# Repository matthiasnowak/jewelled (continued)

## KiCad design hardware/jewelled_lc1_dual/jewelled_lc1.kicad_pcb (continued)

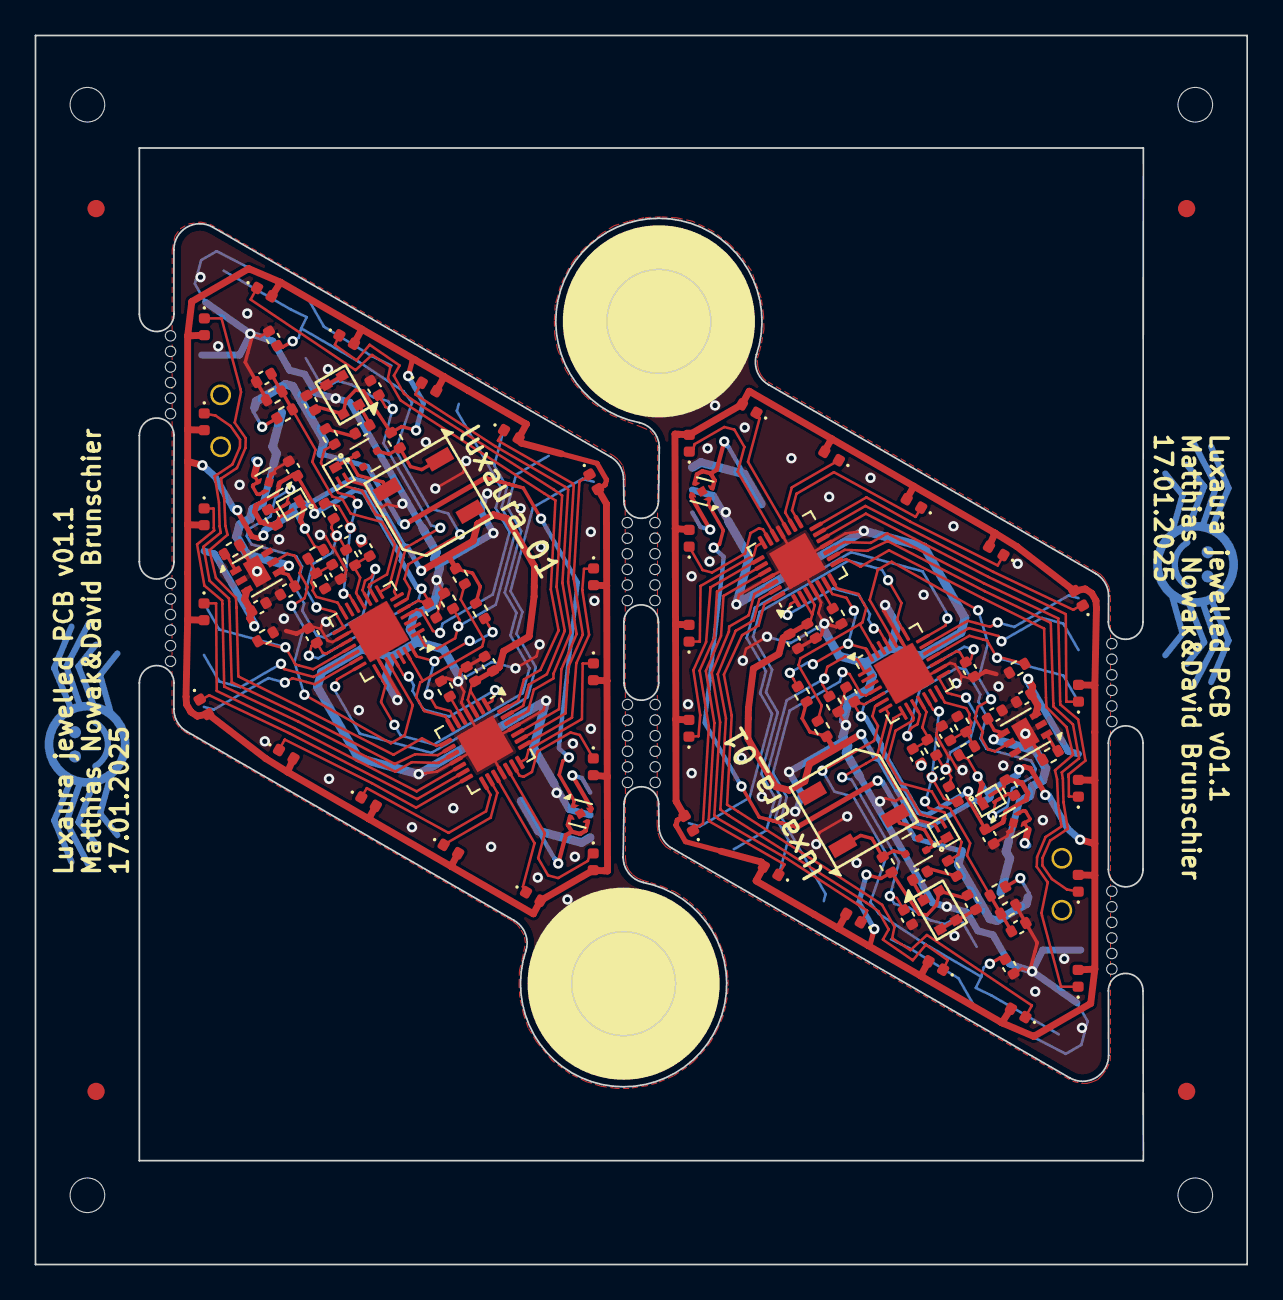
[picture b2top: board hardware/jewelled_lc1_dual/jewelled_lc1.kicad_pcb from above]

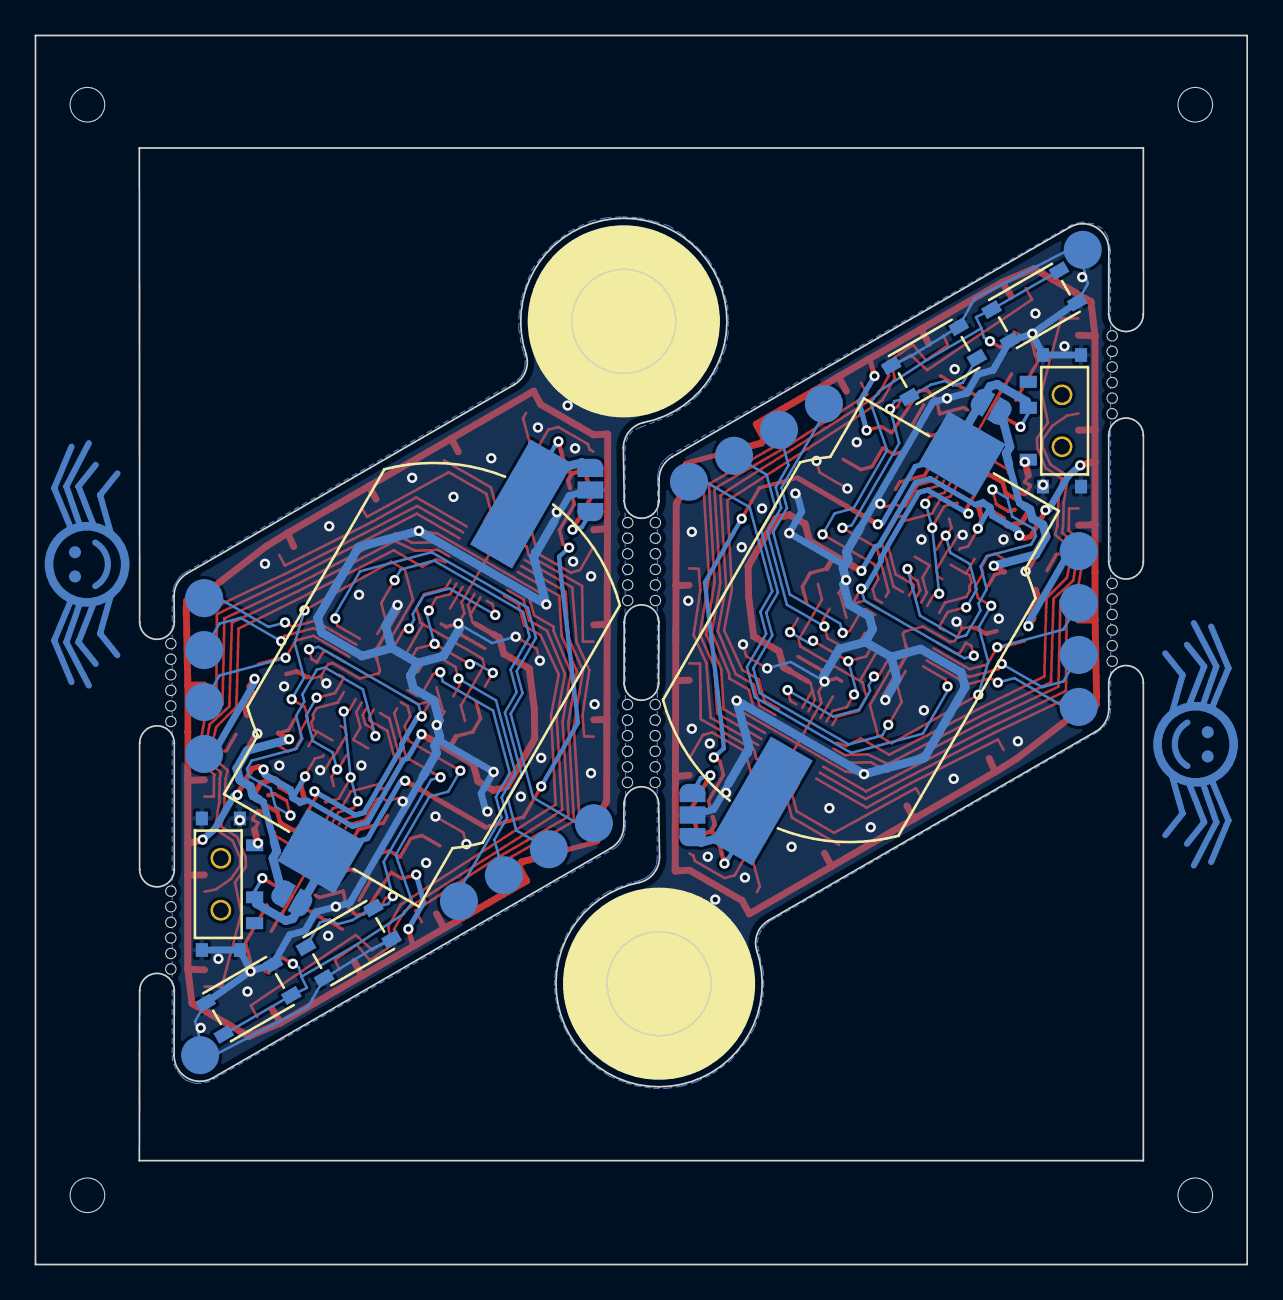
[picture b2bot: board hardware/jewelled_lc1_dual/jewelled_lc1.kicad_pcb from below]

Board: 2 copper layers, 70.0 x 71.0 mm, 148 parts (18 on the bottom side), 106 nets.

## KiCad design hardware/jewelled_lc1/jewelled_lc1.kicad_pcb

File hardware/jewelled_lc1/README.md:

# LuxAura 01 Earring Hardware

## Hardware Overview

- WIP

## Notes

- WIP
- Please note the correct jumper settings to allow either CR2032 or LIR2032 use (bridging the charging circuit)

## Images

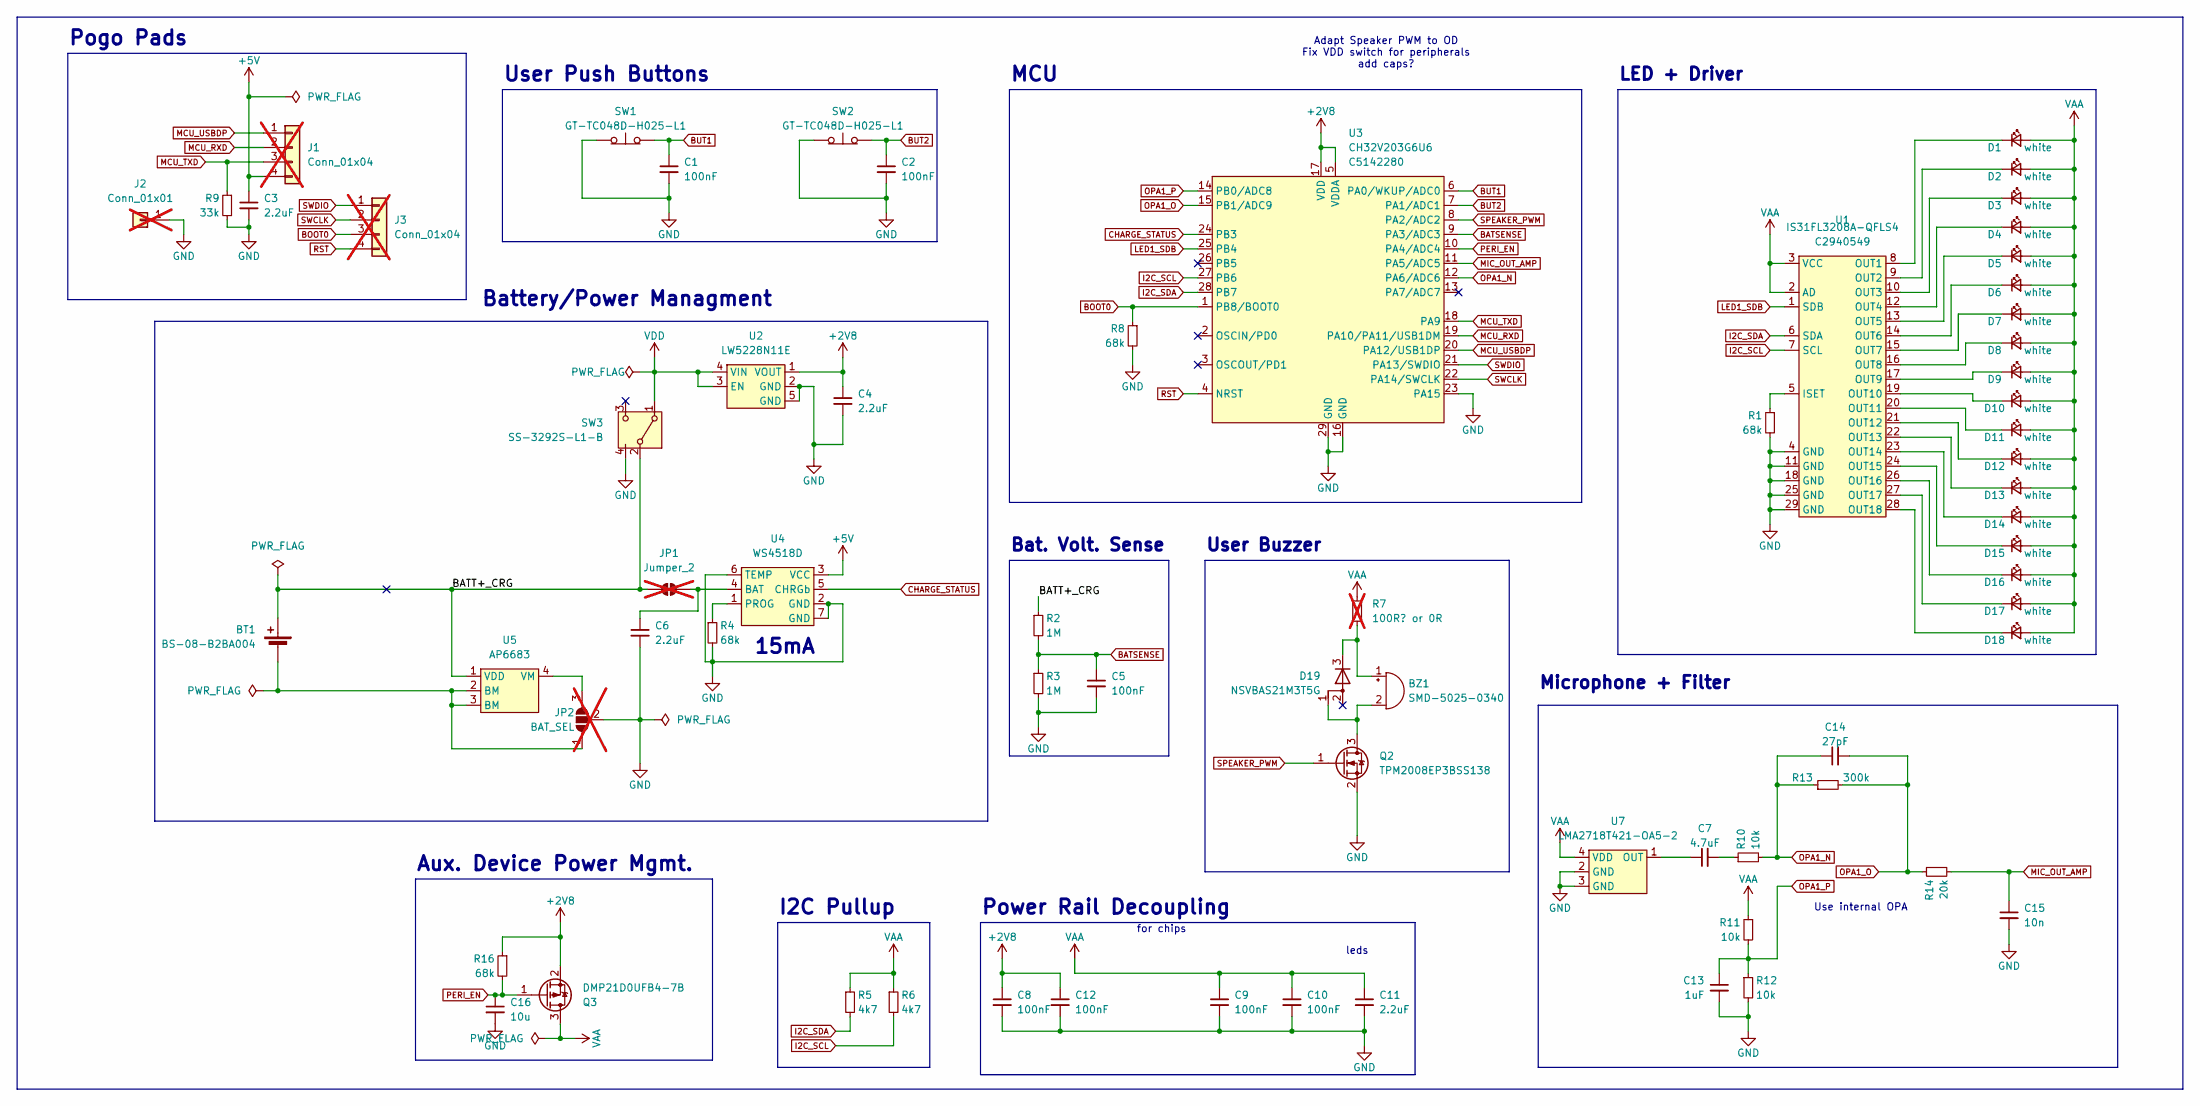
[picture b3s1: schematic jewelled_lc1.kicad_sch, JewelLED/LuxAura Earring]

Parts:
BT1: BS-08-B2BA004; LCSC C964780
BZ1: SMD-5025-0340
C1, C2, C5, C8, C9, C10, C12: 100nF; C_0402_1005Metric; LCSC C100072
C3, C4, C6, C11: 2.2uF; C_0402_1005Metric; LCSC C14445
C7: 4.7uF; C_0402_1005Metric
C13: 1uF; C_0402_1005Metric
C14: 27pF; C_0402_1005Metric
C15: 10n; C_0402_1005Metric
C16: 10u; C_0402_1005Metric; LCSC C14445
D1, D2, D3, D4, D5, D6, D7, D8, D9, D10, D11, D12, D13, D14, D15, D16, D17, D18: white; LED_0402_1005Metric; LCSC C20613596
D19: NSVBAS21M3T5G; SOT-723; LCSC C896450
J1, J3: Conn_01x04; pogo_conn_01x03_P2.0mm_angled; not fitted
J2: Conn_01x01; pogo_conn_01x01_P2.0mm; not fitted
JP1: Jumper_2; SolderJumper-2_P1.3mm_Open_RoundedPad1.0x1.5mm_NoSilk; not fitted
JP2: BAT_SEL; SolderJumper-3_P1.3mm_Open_RoundedPad1.0x1.5mm_NoSilk; not fitted
Q2: TPM2008EP3BSS138; DFN-3_1.0x0.6mm_P0.35mm; MPN C2682293
Q3: DMP21D0UFB4-7B; DFN-3_1.0x0.6mm_P0.35mm; LCSC C155329
R1, R4, R8, R16: 68k; R_0402_1005Metric
R2, R3: 1M; R_0402_1005Metric; LCSC C26083
R5, R6: 4k7; R_0402_1005Metric; LCSC C25940
R7: 100R? or 0R; R_0402_1005Metric; not fitted
R9: 33k; R_0402_1005Metric; MPN C25779; LCSC C25779
R10, R11, R12: 10k; R_0402_1005Metric
R13: 300k; R_0402_1005Metric
R14: 20k; R_0402_1005Metric
SW1, SW2: GT-TC048D-H025-L1; LCSC C843674
SW3: SS-3292S-L1-B; LCSC C2681570
U1: IS31FL3208A-QFLS4; QFN-28-1EP_4x4mm_P0.4mm_EP2.4x2.4mm; MPN C2940549; LCSC C2940551
U2: LW5228N11E; UDFN-4-1EP_1x1mm_P0.65mm_EP0.48x0.48mm; LCSC C20630428
U3: CH32V203G6U6; QFN-28-1EP_4x4mm_P0.4mm_EP2.6x2.6mm; MPN C5142280; LCSC C5142280
U4: WS4518D; DFN-6-1EP_2x2mm_P0.65mm_EP1x1.6mm; LCSC C910991
U5: AP6683; UDFN-4-1EP_1x1mm_P0.65mm_EP0.48x0.48mm; LCSC C2849565
U7: LMA2718T421-OA5-2; ZTS6117H; LCSC C2999748

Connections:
+2V8: C4.1, C8.1, C12.1, Q3.2 (S), R16.1, U2.1 (VOUT), U3.5 (VDDA), U3.17 (VDD)
+5V: C3.1, J1.4, U4.3 (VCC)
/BATT+_CRG: BT1.1 (+), JP1.1 (A), R2.1, SW3.2 (B), U5.1 (VDD)
BATSENSE: C5.1, R2.2, R3.1, U3.9 (PA3/ADC3)
BOOT0: J3.3, R8.1, U3.1 (PB8/BOOT0)
BUT1: C1.1, SW1.2 (B), U3.6 (PA0/WKUP/ADC0)
BUT2: C2.1, SW2.2 (B), U3.7 (PA1/ADC1)
CHARGE_STATUS: U3.24 (PB3), U4.5 (CHRGb)
GND: C1.2, C2.2, C3.2, C4.2, C5.2, C6.2, C8.2, C9.2, C10.2, C11.2, C12.2, C13.2, C15.2, C16.2, J2.1, JP2.2 (C), Q2.2 (S), R1.2, R3.2, R4.2, R8.2, R9.2, R12.2, SW1.1 (A), SW2.1 (A), SW3.4 (B), U1.4 (GND), U1.11 (GND), U1.18 (GND), U1.25 (GND), U1.29 (GND), U2.2 (GND), U2.5 (GND), U3.16 (GND), U3.23 (PA15), U3.29 (GND), U4.2 (GND), U4.6 (TEMP), U4.7 (GND), U7.2 (GND), U7.3 (GND)
I2C_SCL: R6.2, U1.7 (SCL), U3.27 (PB6)
I2C_SDA: R5.2, U1.6 (SDA), U3.28 (PB7)
LED1_SDB: U1.1 (SDB), U3.25 (PB4)
MCU_RXD: J1.2, U3.19 (PA10/PA11/USB1DM)
MCU_TXD: J1.3, R9.1, U3.18 (PA9)
MCU_USBDP: J1.1, U3.20 (PA12/USB1DP)
MIC_OUT_AMP: C15.1, R14.2, U3.11 (PA5/ADC5)
unnamed: BT1.2 (-), JP2.1 (A), U5.2 (BM), U5.3 (BM)
unnamed: BZ1.1 (+), D19.3 (K), R7.2
unnamed: BZ1.2 (-), D19.1 (A), Q2.3 (D)
unnamed: C7.2, R10.1
unnamed: D1.1 (K), U1.8 (OUT1)
unnamed: D2.1 (K), U1.9 (OUT2)
unnamed: D3.1 (K), U1.10 (OUT3)
unnamed: D4.1 (K), U1.12 (OUT4)
unnamed: D5.1 (K), U1.13 (OUT5)
unnamed: D6.1 (K), U1.14 (OUT6)
unnamed: D7.1 (K), U1.15 (OUT7)
unnamed: D8.1 (K), U1.16 (OUT8)
unnamed: D9.1 (K), U1.17 (OUT9)
unnamed: D10.1 (K), U1.19 (OUT10)
unnamed: D11.1 (K), U1.20 (OUT11)
unnamed: D12.1 (K), U1.21 (OUT12)
unnamed: D13.1 (K), U1.22 (OUT13)
unnamed: D14.1 (K), U1.23 (OUT14)
unnamed: D15.1 (K), U1.24 (OUT15)
unnamed: D16.1 (K), U1.26 (OUT16)
unnamed: D17.1 (K), U1.27 (OUT17)
unnamed: D18.1 (K), U1.28 (OUT18)
unnamed: C6.1, JP1.2 (B), U4.4 (BAT)
unnamed: JP2.3 (B), U5.4 (VM)
unnamed: R1.1, U1.5 (ISET)
unnamed: R4.1, U4.1 (PROG)
unnamed: C7.1, U7.1 (OUT)
OPA1_N: C14.1, R10.2, R13.1, U3.12 (PA6/ADC6)
OPA1_O: C14.2, R13.2, R14.1, U3.15 (PB1/ADC9)
OPA1_P: C13.1, R11.2, R12.1, U3.14 (PB0/ADC8)
PERI_EN: C16.1, Q3.1 (G), R16.2, U3.10 (PA4/ADC4)
RST: J3.4, U3.4 (NRST)
SPEAKER_PWM: Q2.1 (G), U3.8 (PA2/ADC2)
SWCLK: J3.2, U3.22 (PA14/SWCLK)
SWDIO: J3.1, U3.21 (PA13/SWDIO)
VAA: C9.1, C10.1, C11.1, D1.2 (A), D2.2 (A), D3.2 (A), D4.2 (A), D5.2 (A), D6.2 (A), D7.2 (A), D8.2 (A), D9.2 (A), D10.2 (A), D11.2 (A), D12.2 (A), D13.2 (A), D14.2 (A), D15.2 (A), D16.2 (A), D17.2 (A), D18.2 (A), Q3.3 (D), R5.1, R6.1, R7.1, R11.1, U1.2 (AD), U1.3 (VCC), U7.4 (VDD)
VDD: SW3.1 (A), U2.3 (EN), U2.4 (VIN)

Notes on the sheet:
leds
User Push Buttons
Use internal OPA
Microphone + Filter
MCU
User Buzzer
Pogo Pads
Battery/Power Managment
15mA
Adapt Speaker PWM to OD Fix VDD switch for peripherals add caps?
LED + Driver
Power Rail Decoupling
Aux. Device Power Mgmt.
I2C Pullup
for chips
Bat. Volt. Sense

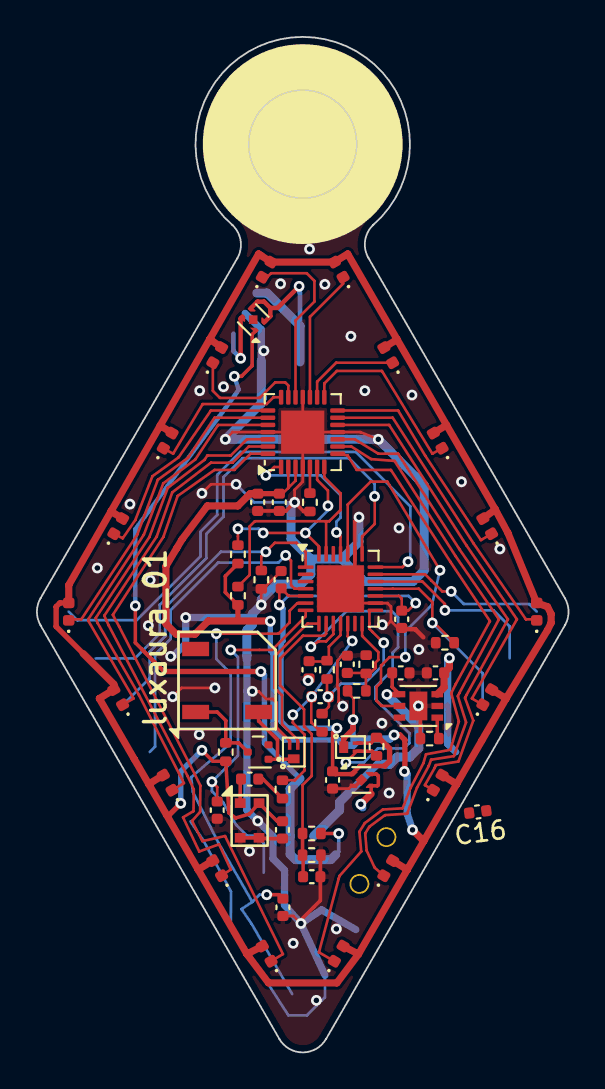
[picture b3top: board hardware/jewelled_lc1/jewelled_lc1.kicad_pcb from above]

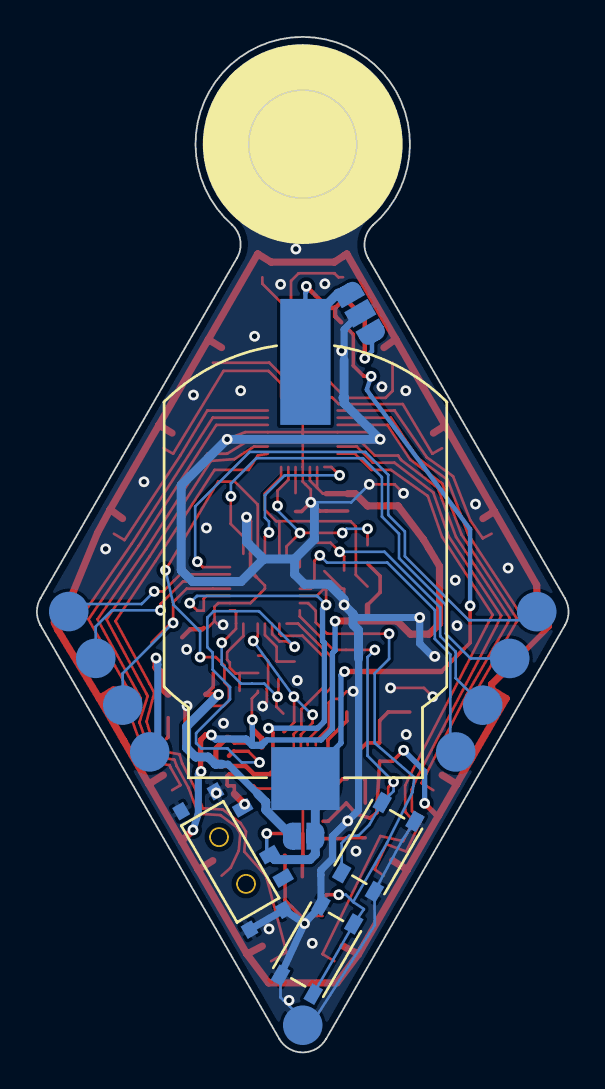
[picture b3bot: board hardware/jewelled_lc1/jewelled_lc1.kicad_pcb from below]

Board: 2 copper layers, 29.5 x 56.4 mm, 68 parts (9 on the bottom side), 53 nets.

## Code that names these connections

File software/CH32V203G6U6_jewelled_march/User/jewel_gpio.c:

/*
 * jewel_gpio.c
 *
 *  Created on: 3 Mar 2025
 *      Author: matth
 */

#include "jewel_gpio.h"

void GPIO_Init_Config(void) {
    RCC_APB2PeriphClockCmd(RCC_APB2Periph_GPIOA, ENABLE);
    RCC_APB2PeriphClockCmd(RCC_APB2Periph_GPIOB, ENABLE);
    GPIO_InitTypeDef GPIO_InitStructure = {0};

    // GPIOB_0:     OPA1_P
    GPIO_InitStructure.GPIO_Pin = IO_OPA_P_PIN;
    GPIO_InitStructure.GPIO_Mode = GPIO_Mode_IN_FLOATING;
    GPIO_InitStructure.GPIO_Speed = GPIO_Speed_10MHz;
    GPIO_Init(IO_OPA_P_PORT, &GPIO_InitStructure);

    // GPIOA_6:     OPA1_N
    GPIO_InitStructure.GPIO_Pin = IO_OPA_N_PIN;
    GPIO_InitStructure.GPIO_Mode = GPIO_Mode_IN_FLOATING;
    GPIO_InitStructure.GPIO_Speed = GPIO_Speed_10MHz;
    GPIO_Init(IO_OPA_N_PORT, &GPIO_InitStructure);

    // GPIOB_1:     Dont init OPA1_OUT1 as GPIO
//    GPIO_InitStructure.GPIO_Pin = IO_OPA_O_PIN;
//    GPIO_InitStructure.GPIO_Mode = GPIO_Mode_AIN;
//    GPIO_InitStructure.GPIO_Speed = GPIO_Speed_10MHz;
//    GPIO_Init(IO_OPA_O_PORT, &GPIO_InitStructure);

    // GPIOA_5:     MICOUT
    GPIO_InitStructure.GPIO_Pin = IO_MICOUT_PIN;
    GPIO_InitStructure.GPIO_Mode = GPIO_Mode_AIN;
    GPIO_InitStructure.GPIO_Speed = GPIO_Speed_10MHz;
    GPIO_Init(IO_MICOUT_PORT, &GPIO_InitStructure);

    // GPIOA_0:     BUT1
    GPIO_InitStructure.GPIO_Pin = GPIO_Pin_0;
    GPIO_InitStructure.GPIO_Mode = GPIO_Mode_IPU;
    GPIO_InitStructure.GPIO_Speed = GPIO_Speed_50MHz;
    GPIO_Init(GPIOA, &GPIO_InitStructure);

    // GPIOA_1:     BUT2
    GPIO_InitStructure.GPIO_Pin = GPIO_Pin_1;
    GPIO_InitStructure.GPIO_Mode = GPIO_Mode_IPU;
    GPIO_InitStructure.GPIO_Speed = GPIO_Speed_50MHz;
    GPIO_Init(IO_BUT2_PORT, &GPIO_InitStructure);

    // GPIOA_2:     BUZZER
    GPIO_StructInit(&GPIO_InitStructure);
    GPIO_InitStructure.GPIO_Pin = IO_BUZZ_PIN;
    GPIO_InitStructure.GPIO_Mode = GPIO_Mode_Out_PP;
    GPIO_InitStructure.GPIO_Speed = GPIO_Speed_10MHz;
    GPIO_Init(IO_BUZZ_PORT, &GPIO_InitStructure);

    //    // GPIOA_4:     PERI_EN
    GPIO_WriteBit(IO_PERI_PORT, IO_PERI_PIN, Bit_SET); // Peripheral off
    GPIO_InitStructure.GPIO_Pin = IO_PERI_PIN;
    GPIO_InitStructure.GPIO_Mode = GPIO_Mode_Out_OD;
    GPIO_InitStructure.GPIO_Speed = GPIO_Speed_10MHz;
    GPIO_Init(IO_PERI_PORT, &GPIO_InitStructure);

    // GPIOA_3:     BATSENSE
    GPIO_StructInit(&GPIO_InitStructure);
    GPIO_InitStructure.GPIO_Pin = IO_BAT_PIN;
    GPIO_InitStructure.GPIO_Mode = GPIO_Mode_AIN;
    GPIO_InitStructure.GPIO_Speed = GPIO_Speed_10MHz;
    GPIO_Init(IO_BAT_PORT, &GPIO_InitStructure);

    // GPIOB_3:     CHARGESTATE
    GPIO_StructInit(&GPIO_InitStructure);
    GPIO_InitStructure.GPIO_Pin = IO_CHARGE_PIN;
    GPIO_InitStructure.GPIO_Mode = GPIO_Mode_IPU;
    GPIO_InitStructure.GPIO_Speed = GPIO_Speed_10MHz;
    GPIO_Init(IO_CHARGE_PORT, &GPIO_InitStructure);

    // GPIOB_8:     BOOT0
    GPIO_StructInit(&GPIO_InitStructure);
    GPIO_InitStructure.GPIO_Pin = IO_BOOT0_PIN;
    GPIO_InitStructure.GPIO_Mode = GPIO_Mode_IN_FLOATING;
    GPIO_InitStructure.GPIO_Speed = GPIO_Speed_10MHz;
    GPIO_Init(IO_BOOT0_PORT, &GPIO_InitStructure);

    // GPIOB_6:     SCL
    GPIO_StructInit(&GPIO_InitStructure);
    GPIO_InitStructure.GPIO_Pin = IO_SCL_PIN;
    GPIO_InitStructure.GPIO_Mode = GPIO_Mode_AF_OD;
    GPIO_InitStructure.GPIO_Speed = GPIO_Speed_50MHz;
    GPIO_Init(IO_SCL_PORT, &GPIO_InitStructure);

    // GPIOB_7:     SDA
    GPIO_StructInit(&GPIO_InitStructure);
    GPIO_InitStructure.GPIO_Pin = IO_SDA_PIN;
    GPIO_InitStructure.GPIO_Mode = GPIO_Mode_AF_OD;
    GPIO_InitStructure.GPIO_Speed = GPIO_Speed_50MHz;
    GPIO_Init(IO_SDA_PORT, &GPIO_InitStructure);

    // GPIOB_7:     SDB
    GPIO_StructInit(&GPIO_InitStructure);
    GPIO_InitStructure.GPIO_Pin = IO_LED_SDB_PIN;
    GPIO_InitStructure.GPIO_Mode = GPIO_Mode_Out_PP;
    GPIO_InitStructure.GPIO_Speed = GPIO_Speed_10MHz;
    GPIO_Init(IO_LED_SDB_PORT, &GPIO_InitStructure);

    // GPIOA_9:     TX
    GPIO_StructInit(&GPIO_InitStructure);
    GPIO_InitStructure.GPIO_Pin = GPIO_Pin_9;
    GPIO_InitStructure.GPIO_Mode = GPIO_Mode_AF_PP;
    //GPIO_InitStructure.GPIO_Mode = GPIO_Mode_IN_FLOATING;
    GPIO_InitStructure.GPIO_Speed = GPIO_Speed_50MHz;
    GPIO_Init(GPIOA, &GPIO_InitStructure);

    // GPIOA_10:     RX
    GPIO_StructInit(&GPIO_InitStructure);
    GPIO_InitStructure.GPIO_Pin = GPIO_Pin_10;
    GPIO_InitStructure.GPIO_Mode = GPIO_Mode_IN_FLOATING;
    GPIO_InitStructure.GPIO_Speed = GPIO_Speed_50MHz;
    GPIO_Init(GPIOA, &GPIO_InitStructure);

    GPIO_StructInit(&GPIO_InitStructure);
    GPIO_InitStructure.GPIO_Pin = GPIO_Pin_13;
    GPIO_InitStructure.GPIO_Mode = GPIO_Mode_IN_FLOATING;
    GPIO_InitStructure.GPIO_Speed = GPIO_Speed_50MHz;
    GPIO_Init(GPIOA, &GPIO_InitStructure);

    GPIO_StructInit(&GPIO_InitStructure);
    GPIO_InitStructure.GPIO_Pin = GPIO_Pin_12;
    GPIO_InitStructure.GPIO_Mode = GPIO_Mode_IN_FLOATING;
    GPIO_InitStructure.GPIO_Speed = GPIO_Speed_50MHz;
    GPIO_Init(GPIOA, &GPIO_InitStructure);

    GPIO_StructInit(&GPIO_InitStructure);
    GPIO_InitStructure.GPIO_Pin = GPIO_Pin_11;
    GPIO_InitStructure.GPIO_Mode = GPIO_Mode_IN_FLOATING;
    GPIO_InitStructure.GPIO_Speed = GPIO_Speed_50MHz;
    GPIO_Init(GPIOA, &GPIO_InitStructure);

    GPIO_StructInit(&GPIO_InitStructure);
    GPIO_InitStructure.GPIO_Pin = GPIO_Pin_14;
    GPIO_InitStructure.GPIO_Mode = GPIO_Mode_IN_FLOATING;
    GPIO_InitStructure.GPIO_Speed = GPIO_Speed_50MHz;
    GPIO_Init(GPIOA, &GPIO_InitStructure);

    GPIO_StructInit(&GPIO_InitStructure);
    GPIO_InitStructure.GPIO_Pin = GPIO_Pin_8;
    GPIO_InitStructure.GPIO_Mode = GPIO_Mode_IN_FLOATING;
    GPIO_InitStructure.GPIO_Speed = GPIO_Speed_50MHz;
    GPIO_Init(GPIOB, &GPIO_InitStructure);
}

void GPIO_Peripheral_Wakeup(void) {
    GPIO_WriteBit(IO_PERI_PORT, IO_PERI_PIN, Bit_RESET);
}

void GPIO_Peripheral_Sleep(void) {
    GPIO_WriteBit(IO_PERI_PORT, IO_PERI_PIN, Bit_SET);
}

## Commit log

2025-07-05 added image ressources
2025-07-05 added jewelled single version hardware
2025-07-05 added jewelled dual version hardware
2025-07-05 added jewelled charging board hardware
2025-07-05 added WIP Software/Firmware for Earrings
2025-07-05 added WIP Software/Firmware for charging board
2025-07-05 Added readmes and license
2025-07-05 added images of pdf exports
2025-07-05 [ImgBot] Optimize images
    *Total -- 12,697.08kb -> 10,720.44kb (15.57%)
    /res/jewelled_pcb_combined.png -- 304.17kb -> 186.68kb (38.63%)
    /res/jewelled_schematic.png -- 950.13kb -> 641.43kb (32.49%)
    /res/jewelled_chargerProgrammer_schematic.png -- 1,140.67kb -> 803.39kb (29.57%)
    /res/jewelled_dual_schematic.png -- 2,183.57kb -> 1,569.04kb (28.14%)
    /res/jewelled_chargerProgrammer_pcb_combined.png -- 557.64kb -> 421.04kb (24.5%)
